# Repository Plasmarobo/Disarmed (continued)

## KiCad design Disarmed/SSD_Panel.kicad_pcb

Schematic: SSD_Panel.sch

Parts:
DS1, DS2, DS3, DS4, DS5, DS6, DS7, DS8: D8014CD; D8041CD
J1: Conn_02x04_Counter_Clockwise; PinSocket_2x04_P2.54mm_Vertical
R1: 2k; R_Axial_DIN0207_L6.3mm_D2.5mm_P15.24mm_Horizontal
U1, U3, U4, U5: MAX7219; DIP-24_W7.62mm
U2: MCP41010; DIP-8_W7.62mm

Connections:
/SSD_Panel/A1: DS1.11, DS2.11, U1.14 (SEG_A)
/SSD_Panel/A2: DS3.11, DS4.11, U3.14 (SEG_A)
/SSD_Panel/A3: DS5.11, DS6.11, U4.14 (SEG_A)
/SSD_Panel/A4: DS7.11, DS8.11, U5.14 (SEG_A)
/SSD_Panel/B1: DS1.7, DS2.7, U1.16 (SEG_B)
/SSD_Panel/B2: DS3.7, DS4.7, U3.16 (SEG_B)
/SSD_Panel/B3: DS5.7, DS6.7, U4.16 (SEG_B)
/SSD_Panel/B4: DS7.7, DS8.7, U5.16 (SEG_B)
/SSD_Panel/C1: DS1.4, DS2.4, U1.20 (SEG_C)
/SSD_Panel/C2: DS3.4, DS4.4, U3.20 (SEG_C)
/SSD_Panel/C3: DS5.4, DS6.4, U4.20 (SEG_C)
/SSD_Panel/C4: DS7.4, DS8.4, U5.20 (SEG_C)
/SSD_Panel/CCSEL: J1.5, U2.1 (~CS)
/SSD_Panel/CLK: J1.3, U1.13 (CLK), U2.2 (SCK), U3.13 (CLK), U4.13 (CLK), U5.13 (CLK)
/SSD_Panel/D1: DS1.2, DS2.2, U1.23 (SEG_D)
/SSD_Panel/D2: DS3.2, DS4.2, U3.23 (SEG_D)
/SSD_Panel/D3: DS5.2, DS6.2, U4.23 (SEG_D)
/SSD_Panel/D4: DS7.2, DS8.2, U5.23 (SEG_D)
/SSD_Panel/DATA: J1.4, U1.1 (DIN), U2.3 (SI)
/SSD_Panel/DIG0: DS1.12, U1.2 (DIG_0)
/SSD_Panel/DIG1: DS1.9, U1.11 (DIG_1)
/SSD_Panel/DIG2: DS1.8, U1.6 (DIG_2)
/SSD_Panel/DIG3: DS1.6, U1.7 (DIG_3)
/SSD_Panel/DIG4: DS2.12, U1.3 (DIG_4)
/SSD_Panel/DIG5: DS2.9, U1.10 (DIG_5)
/SSD_Panel/DIG6: DS2.8, U1.5 (DIG_6)
/SSD_Panel/DIG7: DS2.6, U1.8 (DIG_7)
/SSD_Panel/DIG8: DS3.12, U3.2 (DIG_0)
/SSD_Panel/DIG9: DS3.9, U3.11 (DIG_1)
/SSD_Panel/DIG10: DS3.8, U3.6 (DIG_2)
/SSD_Panel/DIG11: DS3.6, U3.7 (DIG_3)
/SSD_Panel/DIG12: DS4.12, U3.3 (DIG_4)
/SSD_Panel/DIG13: DS4.9, U3.10 (DIG_5)
/SSD_Panel/DIG14: DS4.8, U3.5 (DIG_6)
/SSD_Panel/DIG15: DS4.6, U3.8 (DIG_7)
/SSD_Panel/DIG16: DS5.12, U4.2 (DIG_0)
/SSD_Panel/DIG17: DS5.9, U4.11 (DIG_1)
/SSD_Panel/DIG18: DS5.8, U4.6 (DIG_2)
/SSD_Panel/DIG19: DS5.6, U4.7 (DIG_3)
/SSD_Panel/DIG20: DS6.12, U4.3 (DIG_4)
/SSD_Panel/DIG21: DS6.9, U4.10 (DIG_5)
/SSD_Panel/DIG22: DS6.8, U4.5 (DIG_6)
/SSD_Panel/DIG23: DS6.6, U4.8 (DIG_7)
/SSD_Panel/DIG24: DS7.12, U5.2 (DIG_0)
/SSD_Panel/DIG25: DS7.9, U5.11 (DIG_1)
/SSD_Panel/DIG26: DS7.8, U5.6 (DIG_2)
/SSD_Panel/DIG27: DS7.6, U5.7 (DIG_3)
/SSD_Panel/DIG28: DS8.12, U5.3 (DIG_4)
/SSD_Panel/DIG29: DS8.9, U5.10 (DIG_5)
/SSD_Panel/DIG30: DS8.8, U5.5 (DIG_6)
/SSD_Panel/DIG31: DS8.6, U5.8 (DIG_7)
/SSD_Panel/DP1: DS1.3, DS2.3, U1.22 (SEG_DP)
/SSD_Panel/DP2: DS3.3, DS4.3, U3.22 (SEG_DP)
/SSD_Panel/DP3: DS5.3, DS6.3, U4.22 (SEG_DP)
/SSD_Panel/DP4: DS7.3, DS8.3, U5.22 (SEG_DP)
/SSD_Panel/E1: DS1.1, DS2.1, U1.21 (SEG_E)
/SSD_Panel/E2: DS3.1, DS4.1, U3.21 (SEG_E)
/SSD_Panel/E3: DS5.1, DS6.1, U4.21 (SEG_E)
/SSD_Panel/E4: DS7.1, DS8.1, U5.21 (SEG_E)
/SSD_Panel/F1: DS1.10, DS2.10, U1.15 (SEG_F)
/SSD_Panel/F2: DS3.10, DS4.10, U3.15 (SEG_F)
/SSD_Panel/F3: DS5.10, DS6.10, U4.15 (SEG_F)
/SSD_Panel/F4: DS7.10, DS8.10, U5.15 (SEG_F)
/SSD_Panel/G1: DS1.5, DS2.5, U1.17 (SEG_G)
/SSD_Panel/G2: DS3.5, DS4.5, U3.17 (SEG_G)
/SSD_Panel/G3: DS5.5, DS6.5, U4.17 (SEG_G)
/SSD_Panel/G4: DS7.5, DS8.5, U5.17 (SEG_G)
/SSD_Panel/GND: J1.8, U1.4 (GND), U1.9 (GND), U2.4 (VSS), U2.7 (PB0), U3.4 (GND), U3.9 (GND), U4.4 (GND), U4.9 (GND), U5.4 (GND), U5.9 (GND)
/SSD_Panel/ISET: R1.1, U1.18 (ISET), U3.18 (ISET), U4.18 (ISET), U5.18 (ISET)
/SSD_Panel/LOAD: J1.7, U1.12 (LOAD), U3.12 (LOAD), U4.12 (LOAD), U5.12 (LOAD)
/SSD_Panel/VCC: J1.1, U1.19 (V+), U2.5 (PA0), U2.8 (VDD), U3.19 (V+), U4.19 (V+), U5.19 (V+)
unnamed: R1.2, U2.6 (PW0)
unnamed: U1.24 (DOUT), U3.1 (DIN)
unnamed: U3.24 (DOUT), U4.1 (DIN)
unnamed: U4.24 (DOUT), U5.1 (DIN)

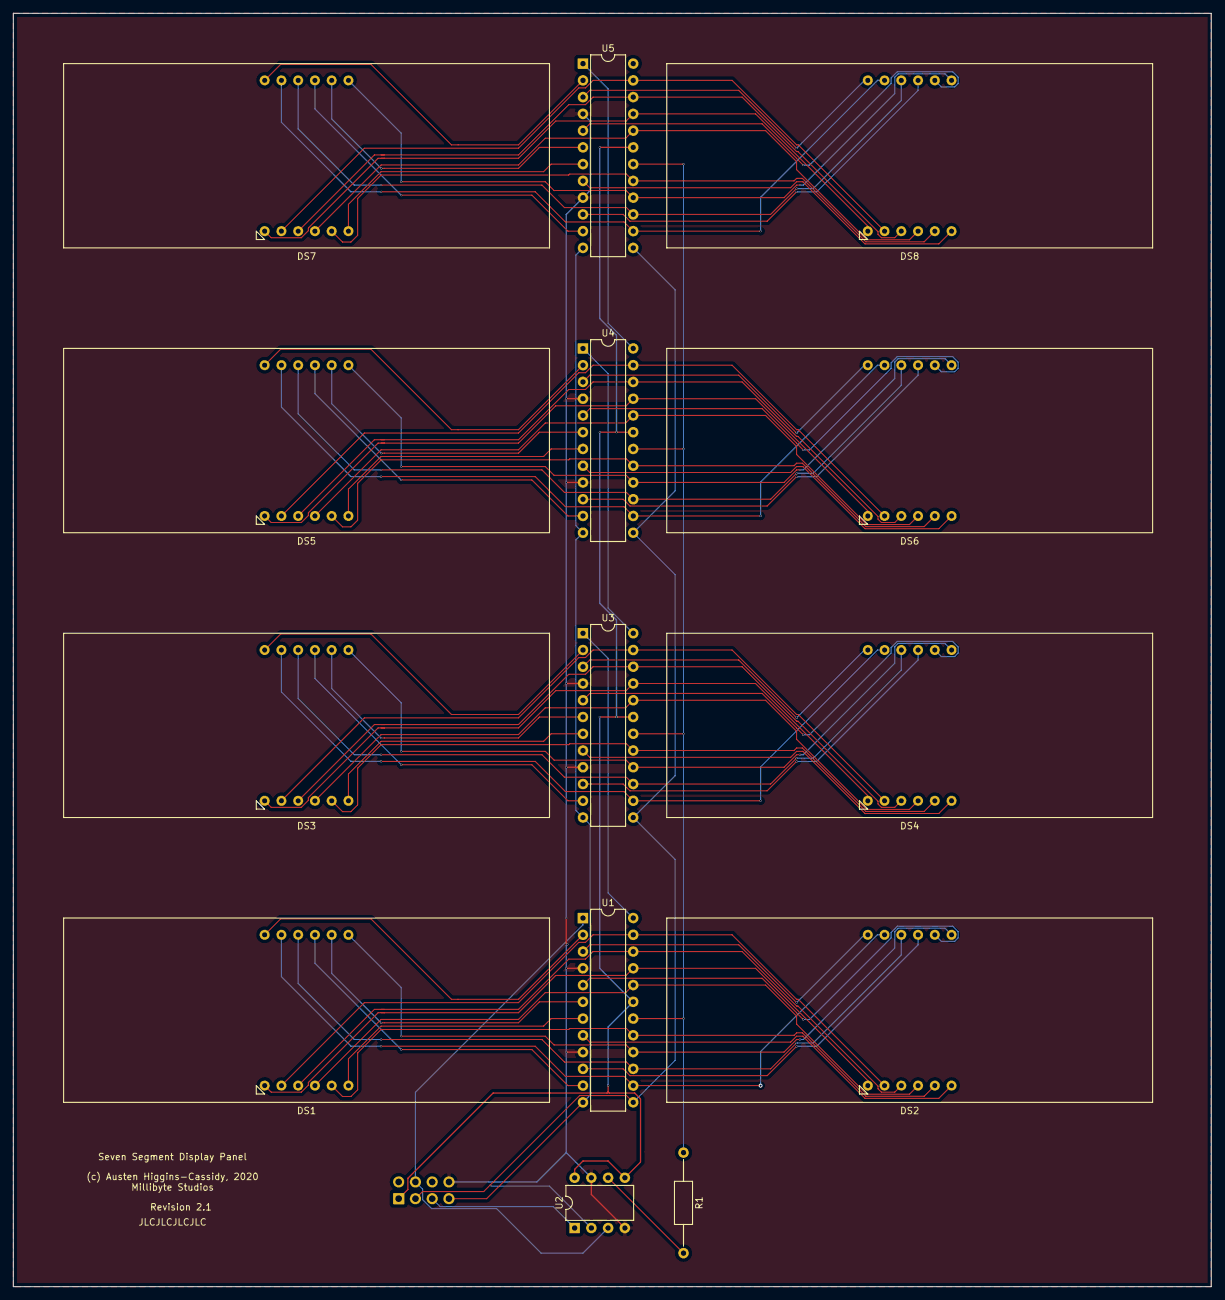
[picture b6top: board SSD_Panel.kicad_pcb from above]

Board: 2 copper layers, 181.6 x 193.0 mm, 15 parts (1 on the bottom side), 75 nets.

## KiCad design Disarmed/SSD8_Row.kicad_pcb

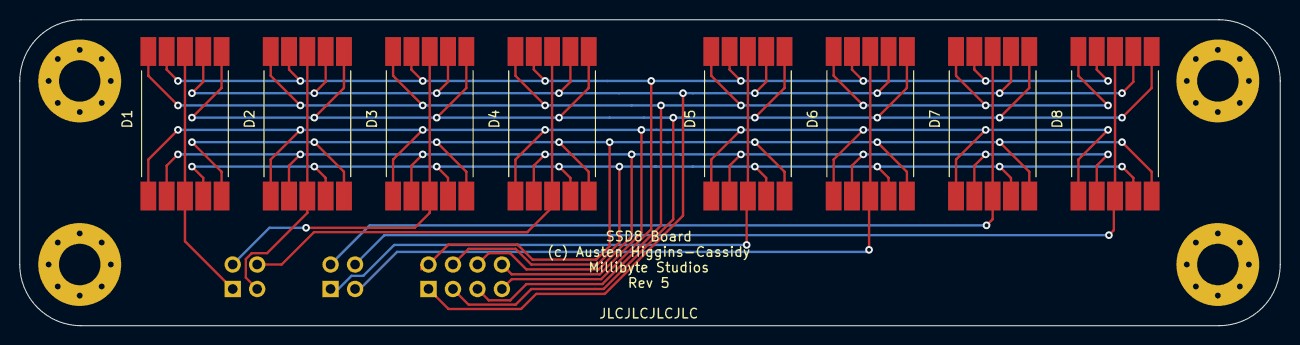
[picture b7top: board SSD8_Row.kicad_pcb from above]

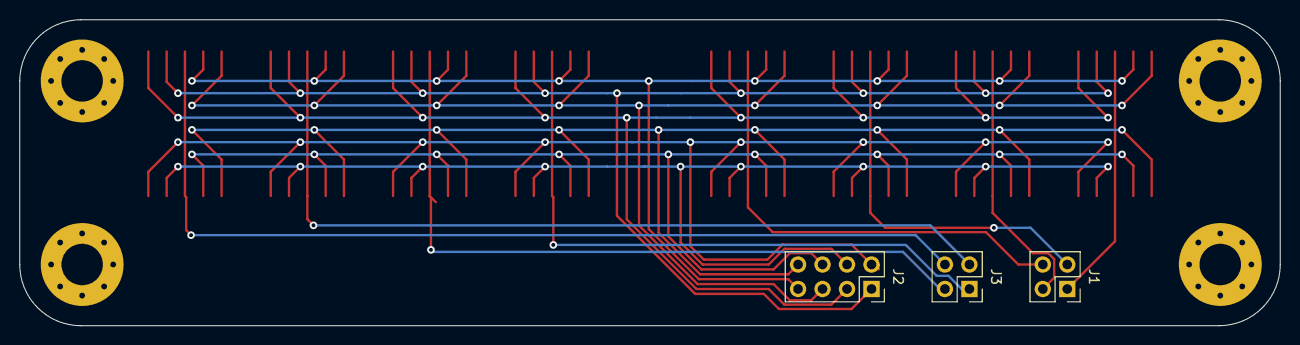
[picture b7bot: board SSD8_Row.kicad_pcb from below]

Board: 2 copper layers, 130.8 x 31.8 mm, 11 parts (3 on the bottom side), 16 nets.

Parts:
D1, D2, D3, D4, D5, D6, D7, D8: HDSP-5500; VDMRX10C0
J1, J3: Conn_02x02_Odd_Even; PinSocket_2x02_P2.54mm_Vertical
J2: Conn_02x04_Odd_Even; PinSocket_2x04_P2.54mm_Vertical

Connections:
/DIG_0: D1.3, D1.8, J1.1
/DIG_1: D2.3, D2.8, J1.3
/DIG_2: D3.3, D3.8, J1.2
/DIG_3: D4.3, D4.8, J1.4
/DIG_4: D5.3, D5.8, J3.1
/DIG_5: D6.3, D6.8, J3.3
/DIG_6: D7.3, D7.8, J3.2
/DIG_7: D8.3, D8.8, J3.4
/SEG_A: D1.7, D2.7, D3.7, D4.7, D5.7, D6.7, D7.7, D8.7, J2.7
/SEG_B: D1.6, D2.6, D3.6, D4.6, D5.6, D6.6, D7.6, D8.6, J2.5
/SEG_C: D1.4, D2.4, D3.4, D4.4, D5.4, D6.4, D7.4, D8.4, J2.6
/SEG_D: D1.2, D2.2, D3.2, D4.2, D5.2, D6.2, D7.2, D8.2, J2.4
/SEG_DP: D1.5, D2.5, D3.5, D4.5, D5.5, D6.5, D7.5, D8.5, J2.8
/SEG_E: D1.1, D2.1, D3.1, D4.1, D5.1, D6.1, D7.1, D8.1, J2.2
/SEG_F: D1.9, D2.9, D3.9, D4.9, D5.9, D6.9, D7.9, D8.9, J2.1
/SEG_G: D1.10, D2.10, D3.10, D4.10, D5.10, D6.10, D7.10, D8.10, J2.3

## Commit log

2016-05-11 :space_invader: Added .gitattributes & .gitignore files
2016-05-29 Test of perhipherals
2020-12-22 Add SSD panel with the SPI Link port
2020-12-22 Footprint update to standard PDIP
2021-01-05 Fix board bug, implement basic driver
2021-01-06 Add readme, include trinket port.
2021-01-06 Add CC license
2021-01-06 Markdown extension
2021-01-07 Wargames Demo
2021-01-13 Add LED Panel
2021-01-25 Board Update
    Add Analog board v1, switch panel v1, remote ssd board v1
2021-03-22 Add new boards
2021-03-22 Add board Images
2021-11-14 Workspace and associated changes
